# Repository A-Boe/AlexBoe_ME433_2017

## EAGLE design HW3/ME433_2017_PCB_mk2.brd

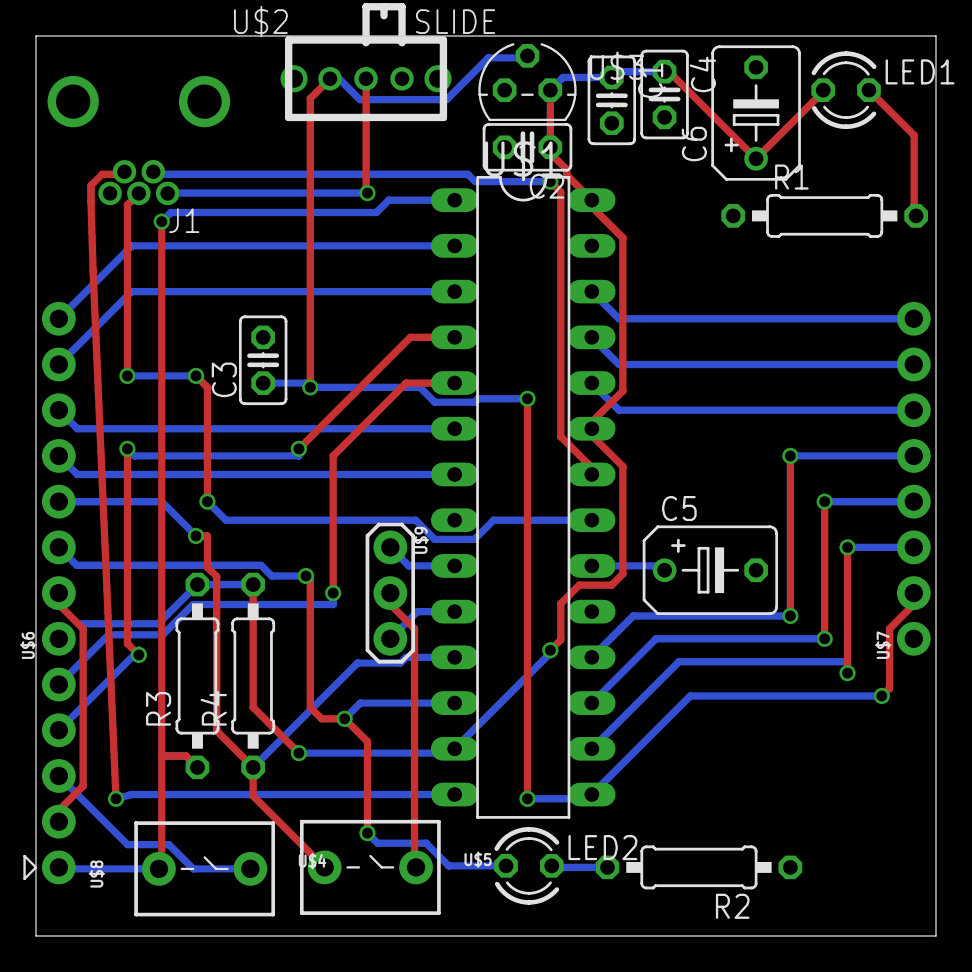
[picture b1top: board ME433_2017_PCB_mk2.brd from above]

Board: 2 copper layers, 50.0 x 50.0 mm, 22 parts (0 on the bottom side), 27 nets.

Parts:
C1, C2, C3, C4: 0.1uF; C025-025X050
C5, C6: 10uF; B45181B
J1: USB-MB-H
LED1: RED; LED3MM
LED2: GREEN; LED3MM
R1, R2: 330; 0207/10
R3, R4: 10k; 0207/10
U$1: PIC32MX250F128B; DIL28-3
U$2: SLIDE
U$3: MCP1702; TO92
U$4: RESET; BUTTON
U$5: USER; BUTTON
U$6, U$7: CONN_08; 1X08
U$8: PICKIT; 1X05
U$9: 8MHz; OSC

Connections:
+3V3: C1.1, C2.1, C4.1, C6.+, LED1.A, R3.2, R4.2, U$1.13, U$1.23, U$1.28, U$3.3, U$6.2, U$8.2
+5V: C3.1, U$1.15, U$2.1, U$3.2, U$7.2
A0: U$1.2, U$6.8
A1: U$1.3, U$6.7
A4/LED: LED2.A, U$1.12, U$6.3
B2: U$1.6, U$6.6
B3: U$1.7, U$6.5
B4/USER: R4.1, U$1.11, U$5.1, U$6.4
B7: U$1.16, U$7.3
B8: U$1.17, U$7.4
B9: U$1.18, U$7.5
B13: U$1.24, U$7.6
B14: U$1.25, U$7.7
B15: U$1.26, U$7.8
D+: J1.D+, U$1.21
D-: J1.D-, U$1.22
GND: C1.2, C2.2, C3.2, C4.2, C5.-, C6.-, J1.GND, R1.1, R2.1, U$1.8, U$1.19, U$1.27, U$3.1, U$4.2, U$5.2, U$6.1, U$7.1, U$8.3, U$9.2
MCLR: R3.1, U$1.1, U$4.1, U$8.1
unnamed: J1.VBUS, U$2.2
unnamed: C5.+, U$1.20
unnamed: LED1.K, R1.2
unnamed: LED2.K, R2.2
unnamed: U$1.9, U$9.1
unnamed: U$1.10, U$9.3
PGC: U$1.5, U$8.5
PGD: U$1.4, U$8.4
USBID: J1.ID, U$1.14

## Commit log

2017-03-27 :neckbeard: Added .gitattributes & .gitignore files
2017-03-27 My first commit!
2017-03-27 One new line
    Added a new line to test the syncing of the repo
2017-03-30 Pictures for hw 1
2017-03-30 Start of hw1 project
2017-03-30 Project for HW 1 finished
2017-04-03 MCP1702 and library
2017-04-03 More HW 2 things
2017-04-10 Schematic and lib
2017-04-10 gerber
2017-04-13 HW 4 code
2017-04-13 HW 4 changes
2017-04-14 Final HW 4
2017-04-17 HW 5 start
2017-04-17 Main file
2017-04-17 Header file
2017-04-17 helper file
2017-04-20 Changes to I2C
2017-04-20 I2C changes
2017-04-20 I2C final mk1
2017-04-20 I2C final mk 2
2017-04-20 I2C final mk 3
2017-04-20 I2c final mk 4
2017-04-20 I2C final mk 5
2017-04-20 I2C final mk 7
2017-04-20 I2C final mk 8
2017-04-20 i2c final mk 9
2017-04-21 I2C final mk 11
2017-04-21 hw 5 schematic
2017-04-21 hw 6 mk1
2017-04-21 hw 6 mk 2
2017-04-21 hw 6 wiring test
2017-04-21 hw 6 mk 3
2017-05-25 hw 6 mk4
2017-05-25 hw 6 mk5
2017-05-25 HW 6 mk 6
2017-05-25 hw 6 mk 7
2017-05-25 hw 6 mk 8
2017-05-25 hw 6 mk 9
2017-05-25 hw 6 mk 10
2017-05-25 hw 6 mk 12
2017-05-25 hw 6 mk 13
2017-05-25 hw 6 mk 14
2017-05-25 hw 6 mk 15
2017-05-27 hw 7 mk 1
2017-05-27 hw 7 mk 2
2017-05-27 hw 7 mk 3
2017-05-27 hw 7 mk 4
2017-05-27 hw 7 mk 5
2017-05-27 hw 7 mk 6
2017-05-27 hw 7 mk 7
2017-05-27 hw 7 mk 8
2017-05-27 hw 8 mk 1
2017-05-27 hw 8 mk 2
2017-06-04 hw 9 init
2017-06-04 hw 9 mk 2 init
2017-06-04 My putty was not working so I hope my code works
    hw 9 final
2017-06-05 Android studio dump
2017-06-05 hw 14 mk 1
2017-06-07 Sorry nick
    Very large dump from working all day(s) to get up to the final/including
    some final stuff
2017-06-10 Final Commit
2017-06-10 wheels
2017-06-10 chassis
    Not the 3 sided box, but someting
2017-06-10 Final wheel used on robot
2017-06-10 Chassis Used
    Not a 3 sideed box
